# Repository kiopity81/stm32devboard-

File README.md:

# STM32F401 Development Board

## Description
STM32F401RET6 development board created using kicad.

## Characteristics
- Power supply via USB Type-C
- Voltage regulator AP2112K-3.3
- SWD connector
- User LED (PA5)
- User button (PA6)
- BOOT0 jumper
- Reset circuit

## Status
- Schematic is completed
- ERC check passed with no errors..
- PCB design is in process, placement is almost done

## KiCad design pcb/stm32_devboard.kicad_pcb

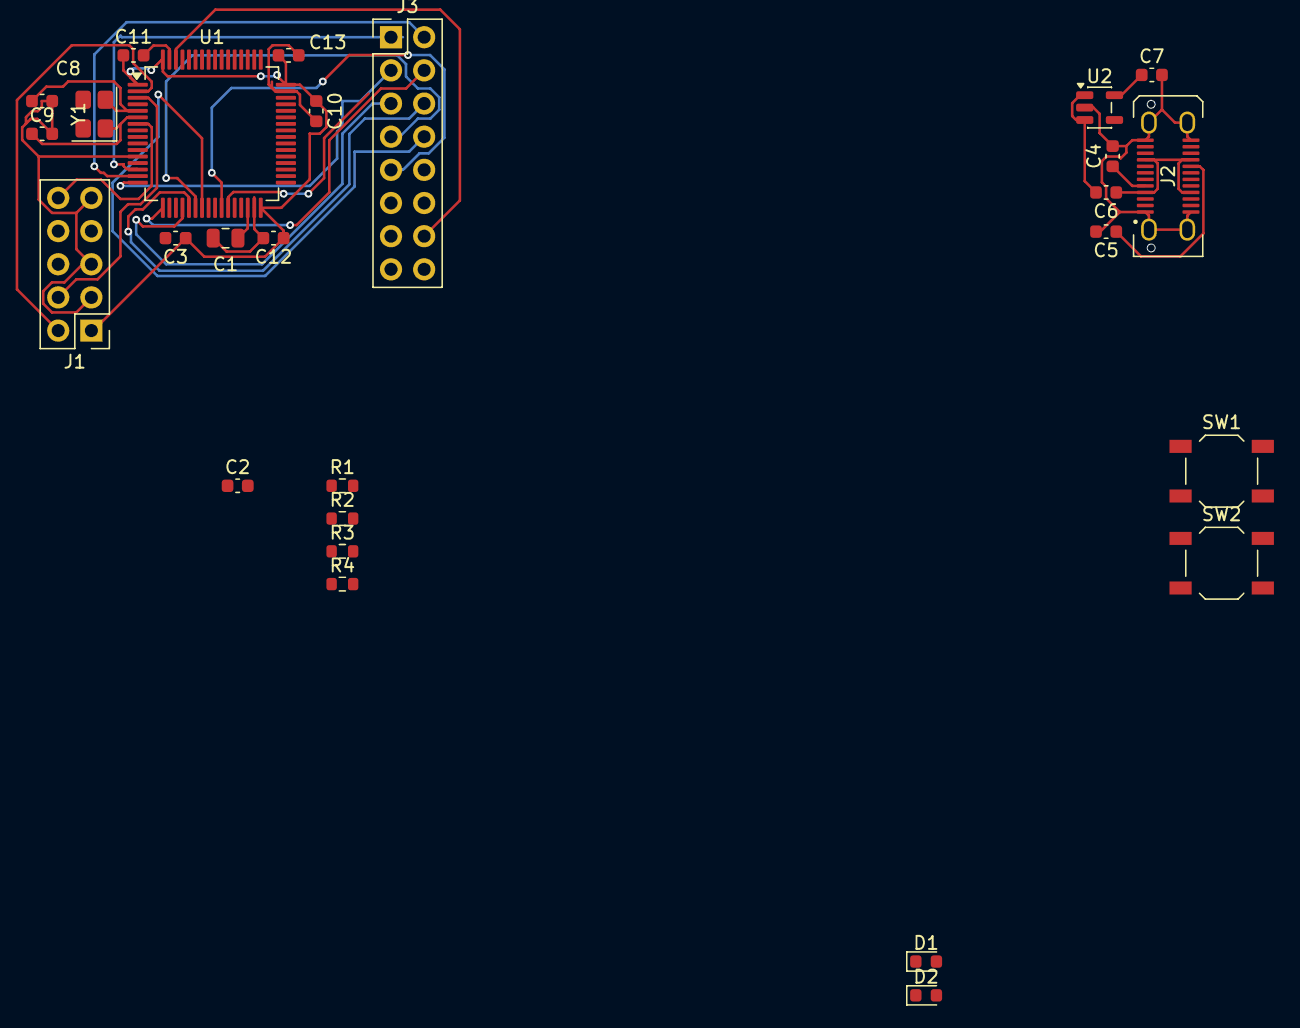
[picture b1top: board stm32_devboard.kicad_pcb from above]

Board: 2 copper layers, 27 parts (0 on the bottom side), 29 nets.

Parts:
C1: 2.2u; C_0805_2012Metric
C2, C3, C10, C11, C12: 100n; C_0603_1608Metric
C4, C5: 5.1K; C_0603_1608Metric
C6, C7: 1u; C_0603_1608Metric
C8, C9: 22p; C_0603_1608Metric
C13: 4.7u; C_0603_1608Metric
D1, D2: LED; LED_0603_1608Metric
J1: Conn_ARM_JTAG_SWD_10; PinHeader_2x05_P2.54mm_Vertical
J2: USB_C_Receptacle_USB2.0_14P; USB_C_Receptacle_JAE_DX07S024WJ3R400
J3: Conn_01x16; PinHeader_2x08_P2.54mm_Vertical
R1: 10K; R_0603_1608Metric
R2, R3: 330; R_0603_1608Metric
R4: 1K; R_0603_1608Metric
SW1, SW2: SW_Push; SW_SPST_TL3342
U1: STM32F401RETx; LQFP-64_10x10mm_P0.5mm
U2: AP2112K-3.3; SOT-23-5
Y1: 8 MHz; Crystal_SMD_3225-4Pin_3.2x2.5mm

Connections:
+3.3V: C3.1, C7.1, C10.1, C11.1, C12.1, C13.1, J1.1 (VTref), J3.15, R3.1, R4.1, U1.1 (VBAT), U1.19 (VDD), U1.32 (VDD), U1.48 (VDD), U1.64 (VDD), U2.5 (VOUT)
/NRST: C2.1, J1.10 (~RESET), SW1.2, U1.7 (NRST)
/SWCLK: J1.4 (SWCLK/TCK), U1.3 (PC14)
/SWDIO: J1.2 (SWDIO/TMS), U1.2 (PC13)
/USER_BUTTON: J3.7, R3.2, SW2.1, U1.22 (PA6)
/USER_LED: J3.6, R2.1, U1.21 (PA5)
/boot0: R1.1, U1.60 (BOOT0)
GND: C1.1, C2.2, C3.2, C4.2, C5.2, C7.2, C8.2, C9.2, C10.2, C11.2, C12.2, C13.2, D1.1 (K), D2.1 (K), J1.3 (GND), J1.5 (GND), J1.9 (GNDDetect), J2.A1 (GND), J2.A12 (GND), J2.B1 (GND), J2.B12 (GND), J2.SH (SHIELD), J3.16, R1.2, SW1.1, SW2.2, U1.12 (VSSA), U1.18 (VSS), U1.31 (VSS), U1.47 (VSS), U1.63 (VSS), U2.2 (GND)
unnamed: C6.1, J2.A4 (VBUS), J2.A9 (VBUS), J2.B4 (VBUS), J2.B9 (VBUS)
unnamed: D1.2 (A), R2.2
unnamed: D2.2 (A), R4.2
unnamed: C4.1, J2.A5 (CC1)
unnamed: C5.1, J2.B5 (CC2)
unnamed: J3.1, U1.14 (PA0)
unnamed: J3.2, U1.15 (PA1)
unnamed: J3.3, U1.16 (PA2)
unnamed: J3.4, U1.17 (PA3)
unnamed: J3.5, U1.20 (PA4)
unnamed: J3.8, U1.23 (PA7)
unnamed: J3.9, U1.26 (PB0)
unnamed: J3.10, U1.27 (PB1)
unnamed: J3.11, U1.58 (PB6)
unnamed: J3.12, U1.59 (PB7)
unnamed: J3.13, U1.61 (PB8)
unnamed: J3.14, U1.62 (PB9)
unnamed: C8.1, U1.5 (PH0), Y1.2
unnamed: C9.1, U1.6 (PH1), Y1.1
unnamed: C1.2, U1.30 (VCAP1)
unnamed: C6.2, U2.1 (VIN), U2.3 (EN)
